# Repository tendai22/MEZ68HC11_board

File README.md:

# MEZ68HC11_board
MC68HC11 mezzanine board for EMUZ80 series

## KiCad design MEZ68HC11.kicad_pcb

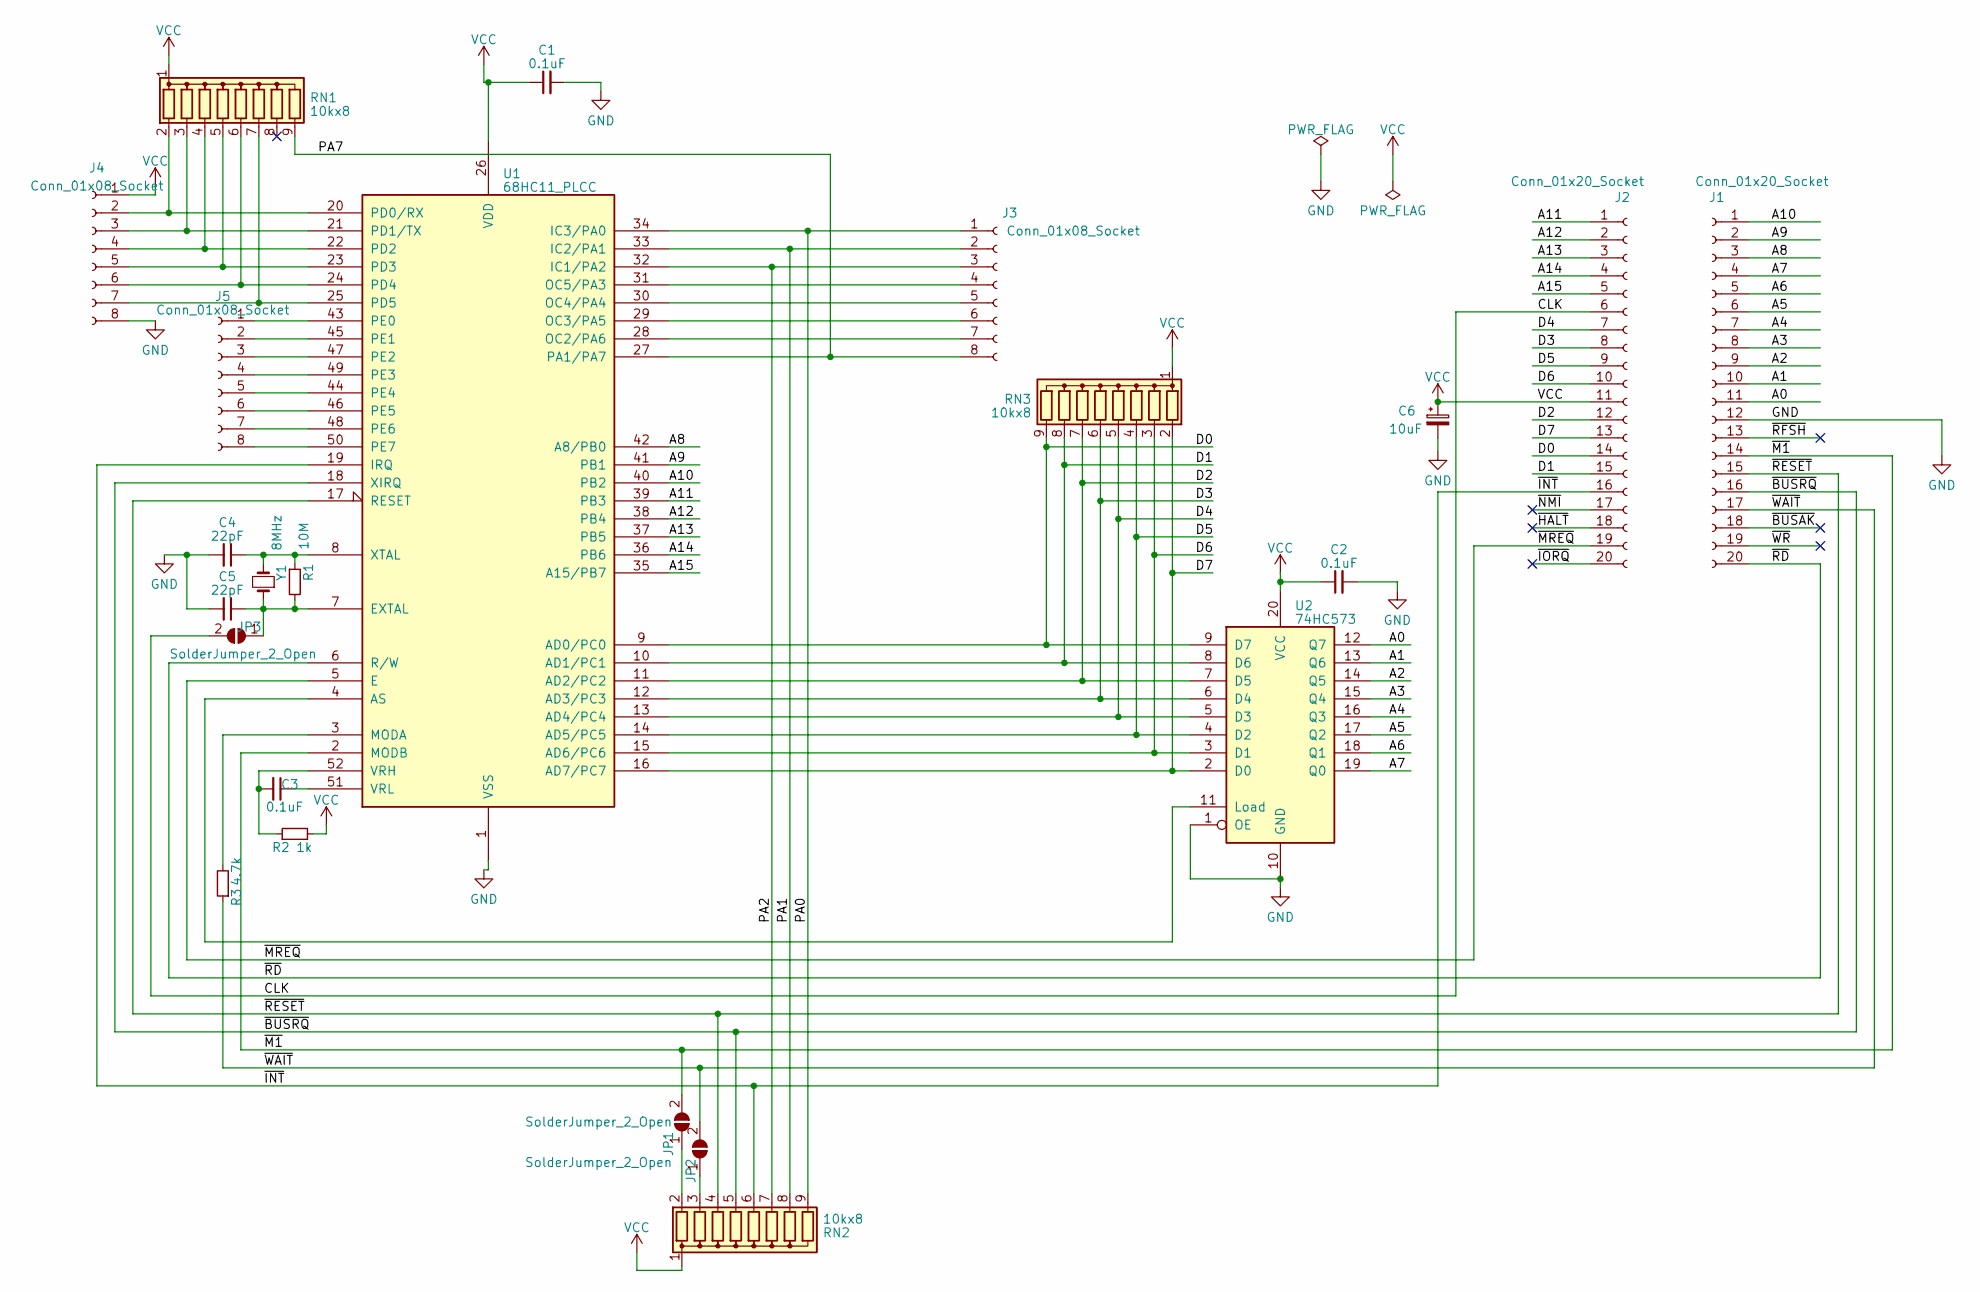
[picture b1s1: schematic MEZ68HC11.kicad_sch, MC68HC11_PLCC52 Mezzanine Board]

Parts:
C1, C2, C3: 0.1uF; C_Disc_D3.0mm_W1.6mm_P2.50mm
C4, C5: 22pF; C_Disc_D3.0mm_W1.6mm_P2.50mm
C6: 10uF; CP_Radial_D4.0mm_P2.00mm
J1, J2: Conn_01x20_Socket; PinSocket_1x20_P2.54mm_Vertical
J3, J4, J5: Conn_01x08_Socket; PinSocket_1x08_P2.54mm_Vertical
JP1, JP2, JP3: SolderJumper_2_Open; SolderJumper-2_P1.3mm_Open_RoundedPad1.0x1.5mm
R1: 10M; R_Axial_DIN0204_L3.6mm_D1.6mm_P7.62mm_Horizontal
R2: 1k; R_Axial_DIN0204_L3.6mm_D1.6mm_P7.62mm_Horizontal
R3: 4.7k; R_Axial_DIN0204_L3.6mm_D1.6mm_P7.62mm_Horizontal
RN1, RN2, RN3: 10kx8; R_Array_SIP9
U1: 68HC11_PLCC; PLCC-52
U2: 74HC573; DIP-20_W7.62mm
Y1: 8MHz; Crystal_HC49-U_Vertical

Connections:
/A0: J1.11, U2.12 (Q7)
/A1: J1.10, U2.13 (Q6)
/A2: J1.9, U2.14 (Q5)
/A3: J1.8, U2.15 (Q4)
/A4: J1.7, U2.16 (Q3)
/A5: J1.6, U2.17 (Q2)
/A6: J1.5, U2.18 (Q1)
/A7: J1.4, U2.19 (Q0)
/A8: J1.3, U1.42 (A8/PB0)
/A9: J1.2, U1.41 (PB1)
/A10: J1.1, U1.40 (PB2)
/A11: J2.1, U1.39 (PB3)
/A12: J2.2, U1.38 (PB4)
/A13: J2.3, U1.37 (PB5)
/A14: J2.4, U1.36 (PB6)
/A15: J2.5, U1.35 (A15/PB7)
/CLK: J2.6, JP3.2 (B)
/D0: J2.14, RN3.9 (R8), U1.9 (AD0/PC0), U2.9 (D7)
/D1: J2.15, RN3.8 (R7), U1.10 (AD1/PC1), U2.8 (D6)
/D2: J2.12, RN3.7 (R6), U1.11 (AD2/PC2), U2.7 (D5)
/D3: J2.8, RN3.6 (R5), U1.12 (AD3/PC3), U2.6 (D4)
/D4: J2.7, RN3.5 (R4), U1.13 (AD4/PC4), U2.5 (D3)
/D5: J2.9, RN3.4 (R3), U1.14 (AD5/PC5), U2.4 (D2)
/D6: J2.10, RN3.3 (R2), U1.15 (AD6/PC6), U2.3 (D1)
/D7: J2.13, RN3.2 (R1), U1.16 (AD7/PC7), U2.2 (D0)
/PA0: J3.1, RN2.9 (R8), U1.34 (IC3/PA0)
/PA1: J3.2, RN2.8 (R7), U1.33 (IC2/PA1)
/PA2: J3.3, RN2.7 (R6), U1.32 (IC1/PA2)
/PA7: J3.8, RN1.9 (R8), U1.27 (PA1/PA7)
/~BUSAK: J1.18
/~BUSRQ: J1.16, RN2.5 (R4), U1.18 (XIRQ)
/~HALT: J2.18
/~INT: J2.16, RN2.6 (R5), U1.19 (IRQ)
/~IORQ: J2.20
/~M1: J1.14, JP1.2 (B), U1.2 (MODB)
/~MREQ: J2.19, U1.5 (E)
/~NMI: J2.17
/~RD: J1.20, U1.6 (R/W)
/~RESET: J1.15, RN2.4 (R3), U1.17 (RESET)
/~RFSH: J1.13
/~WAIT: J1.17, JP2.2 (B), R3.1
/~WR: J1.19
GND: C1.2, C2.2, C4.2, C5.2, C6.2, J1.12, J4.8, U1.1 (VSS), U2.1 (OE), U2.10 (GND)
unnamed: J3.4, U1.31 (OC5/PA3)
unnamed: J3.5, U1.30 (OC4/PA4)
unnamed: J3.6, U1.29 (OC3/PA5)
unnamed: J3.7, U1.28 (OC2/PA6)
unnamed: J4.2, RN1.2 (R1), U1.20 (PD0/RX)
unnamed: J4.3, RN1.3 (R2), U1.21 (PD1/TX)
unnamed: J4.4, RN1.4 (R3), U1.22 (PD2)
unnamed: J4.5, RN1.5 (R4), U1.23 (PD3)
unnamed: J4.6, RN1.6 (R5), U1.24 (PD4)
unnamed: J4.7, RN1.7 (R6), U1.25 (PD5)
unnamed: J5.1, U1.43 (PE0)
unnamed: J5.2, U1.45 (PE1)
unnamed: J5.3, U1.47 (PE2)
unnamed: J5.4, U1.49 (PE3)
unnamed: J5.5, U1.44 (PE4)
unnamed: J5.6, U1.46 (PE5)
unnamed: J5.7, U1.48 (PE6)
unnamed: J5.8, U1.50 (PE7)
unnamed: JP1.1 (A), RN2.2 (R1)
unnamed: JP2.1 (A), RN2.3 (R2)
unnamed: C5.1, JP3.1 (A), R1.2, U1.7 (EXTAL), Y1.1
unnamed: U1.4 (AS), U2.11 (Load)
unnamed: R3.2, U1.3 (MODA)
unnamed: C3.2, R2.1, U1.52 (VRH)
unnamed: C3.1, U1.51 (VRL)
unnamed: C4.1, R1.1, U1.8 (XTAL), Y1.2
VCC: C1.1, C2.1, C6.1, J2.11, J4.1, R2.2, RN1.1 (common), RN2.1 (common), RN3.1 (common), U1.26 (VDD), U2.20 (VCC)

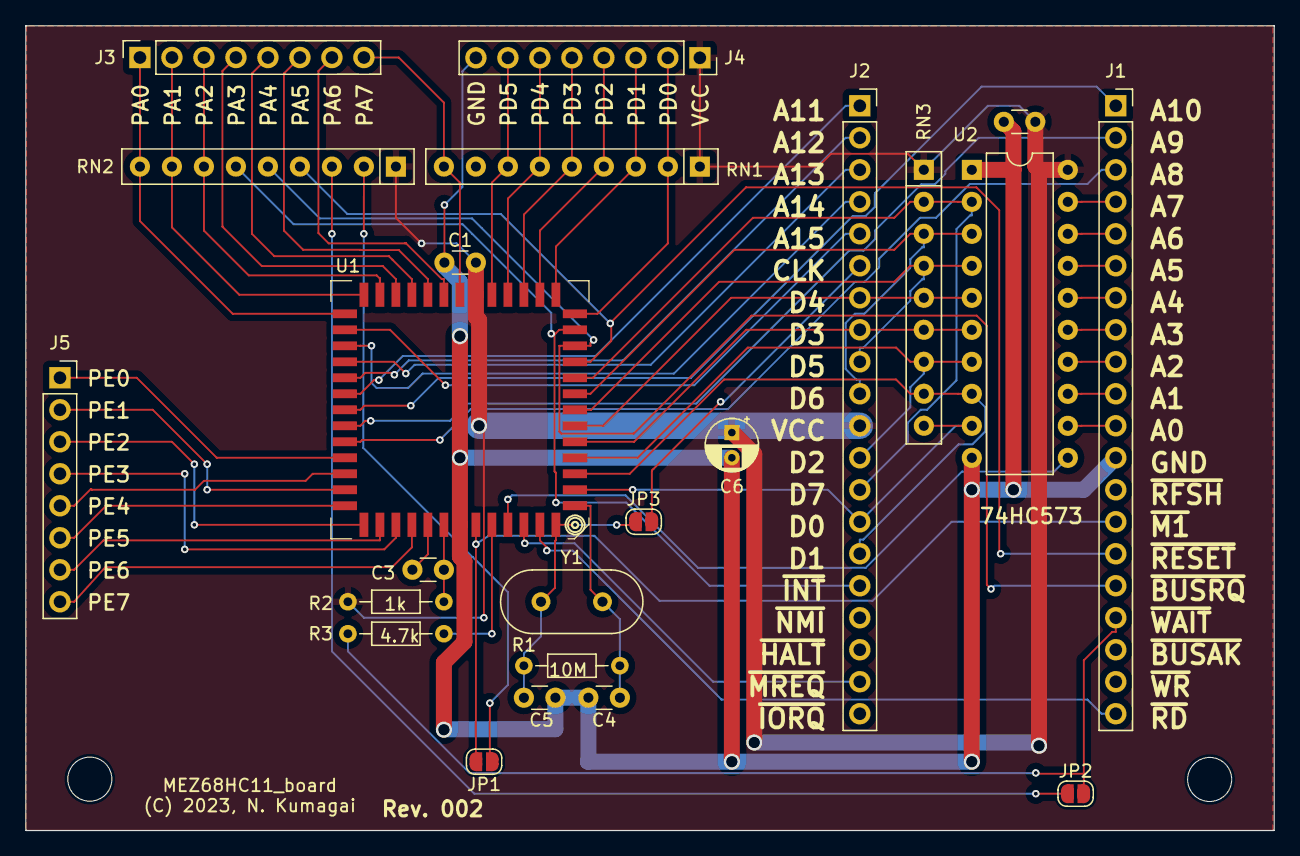
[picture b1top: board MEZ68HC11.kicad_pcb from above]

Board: 2 copper layers, 99.1 x 63.9 mm, 25 parts (0 on the bottom side), 64 nets.

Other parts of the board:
H2, H4: MountingHole; MountingHole_3.5mm

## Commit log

2023-09-06 Initial commit, schematic draft finished
2023-09-07 add some in the schematics
2023-09-07 Rev001. ordered to JCLPCB
2023-09-08 add 4.7k between MODA and PIC

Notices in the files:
MEZ68HC11.kicad_pcb:
(C) 2023, N. Kumagai
